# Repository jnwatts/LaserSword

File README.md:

# LaserSword
Advanced replacement logic board for a $7 "laser sword"

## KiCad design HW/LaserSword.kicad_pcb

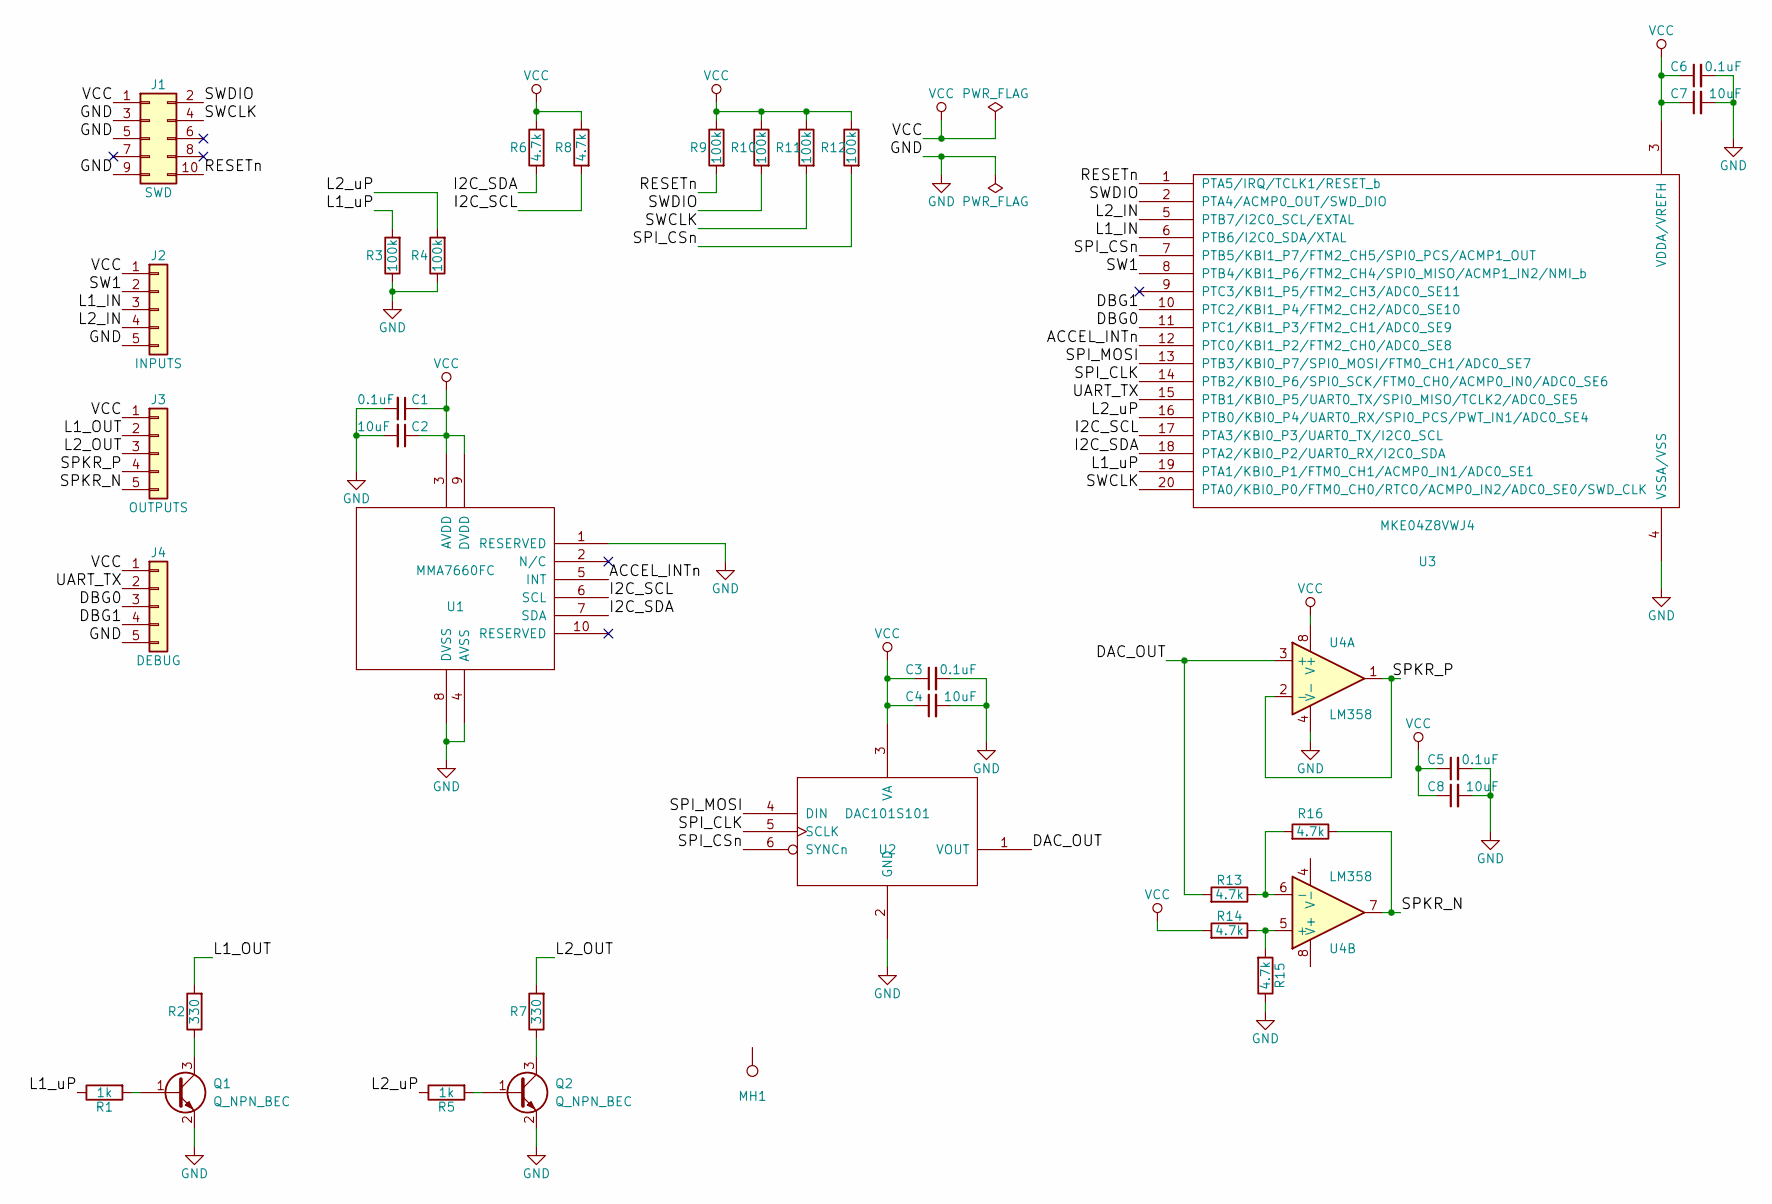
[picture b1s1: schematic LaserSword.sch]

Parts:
C1, C3, C5, C6: 0.1uF; C_0603_HandSoldering
C2, C4, C7, C8: 10uF; C_0603_HandSoldering
J1: SWD; Pin_Header_Straight_2x05_Pitch1.27mm; digikey# SAM9430-ND
J2: INPUTS; Pin_Header_Straight_1x05_Pitch1.00mm; MfrPart SMH100-LPSE-Sxx-ST-BK; digikey# S9215-ND
J3: OUTPUTS; Pin_Header_Straight_1x05_Pitch1.00mm; MfrPart SMH100-LPSE-Sxx-ST-BK; digikey# S9215-ND
J4: DEBUG; Pin_Header_Straight_1x05_Pitch1.00mm; MfrPart SMH100-LPSE-Sxx-ST-BK; digikey# S9215-ND
MH1: MH1; MountingHole_2.2mm_M2
Q1, Q2: Q_NPN_BEC; SOT-23; MfrPart MMBT3904TPMSCT; digikey# MMBT3904TPMSCT-ND
R1, R5: 1k; R_0603_HandSoldering
R2, R7: 330; R_0603_HandSoldering
R3, R4, R9, R10, R11, R12: 100k; R_0603_HandSoldering
R6, R8, R13, R14, R15, R16: 4.7k; R_0603_HandSoldering
U1: MMA7660FC; DFN-10_3x3mm_Pitch0.5mm; MfrPart MMA7660FCT; digikey# MMA7660FCT-ND
U2: DAC101S101; SOT-23-6_Handsoldering; MfrPart DAC101S101CIMK/NOPB; digikey# DAC101S101CIMK/NOPBCT-ND
U3: MKE04Z8VWJ4; SO-20_12.8x7.5mm_Pitch1.27mm; MfrPart MKE04Z8VWJ4; digikey# MKE04Z8VWJ4-ND
U4: LM358; SOIC-8_3.9x4.9mm_Pitch1.27mm; MfrPart LMV358DR2G; digikey# LMV358DR2GOSCT-ND

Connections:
/ACCEL_INTn: U1.5 (INT), U3.12 (PTC0/KBI1_P2/FTM2_CH0/ADC0_SE8)
/DAC_OUT: R13.2, U2.1 (VOUT), U4.3 (+)
/DBG0: J4.3, U3.11 (PTC1/KBI1_P3/FTM2_CH1/ADC0_SE9)
/DBG1: J4.4, U3.10 (PTC2/KBI1_P4/FTM2_CH2/ADC0_SE10)
/I2C_SCL: R8.2, U1.6 (SCL), U3.17 (PTA3/KBI0_P3/UART0_TX/I2C0_SCL)
/I2C_SDA: R6.2, U1.7 (SDA), U3.18 (PTA2/KBI0_P2/UART0_RX/I2C0_SDA)
/L1_IN: J2.3, U3.6 (PTB6/I2C0_SDA/XTAL)
/L1_OUT: J3.2, R2.2
/L1_uP: R1.1, R3.2, U3.19 (PTA1/KBI0_P1/FTM0_CH1/ACMP0_IN1/ADC0_SE1)
/L2_IN: J2.4, U3.5 (PTB7/I2C0_SCL/EXTAL)
/L2_OUT: J3.3, R7.2
/L2_uP: R4.2, R5.1, U3.16 (PTB0/KBI0_P4/UART0_RX/SPI0_PCS/PWT_IN1/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)
/RESETn: J1.10, R9.2, U3.1 (PTA5/IRQ/TCLK1/RESET_b)
/SPI_CLK: U2.5 (SCLK), U3.14 (PTB2/KBI0_P6/SPI0_SCK/FTM0_CH0/ACMP0_IN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)
/SPI_CSn: R12.2, U2.6 (SYNCn), U3.7 (PTB5/KBI1_P7/FTM2_CH5/SPI0_PCS/ACMP1_OUT)
/SPI_MOSI: U2.4 (DIN), U3.13 (PTB3/KBI0_P7/SPI0_MOSI/FTM0_CH1/ADC0_SE7)
/SPKR_N: J3.5, R16.1, U4.7
/SPKR_P: J3.4, U4.1, U4.2 (-)
/SW1: J2.2, U3.8 (PTB4/KBI1_P6/FTM2_CH4/SPI0_MISO/ACMP1_I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)
/SWCLK: J1.4, R11.2, U3.20 (PTA0/KBI0_P0/FTM0_CH0/RTCO/ACMP0_IN2/AD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)
/SWDIO: J1.2, R10.2, U3.2 (PTA4/ACMP0_OUT/SWD_DIO)
/UART_TX: J4.2, U3.15 (PTB1/KBI0_P5/UART0_TX/SPI0_MISO/TCLK2/A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)
GND: C1.2, C2.2, C3.2, C4.2, C5.2, C6.2, C7.2, C8.2, J1.3, J1.5, J1.9, J2.5, J4.5, Q1.2 (E), Q2.2 (E), R3.1, R4.1, R15.1, U1.1 (RESERVED), U1.4 (AVSS), U1.8 (DVSS), U2.2 (GND), U3.4 (VSSA/VSS), U4.4 (V-)
unnamed: Q1.1 (B), R1.2
unnamed: Q1.3 (C), R2.1
unnamed: Q2.1 (B), R5.2
unnamed: Q2.3 (C), R7.1
unnamed: R13.1, R16.2, U4.6 (-)
unnamed: R14.1, R15.2, U4.5 (+)
VCC: C1.1, C2.1, C3.1, C4.1, C5.1, C6.1, C7.1, C8.1, J1.1, J2.1, J3.1, J4.1, R6.1, R8.1, R9.1, R10.1, R11.1, R12.1, R14.2, U1.3 (AVDD), U1.9 (DVDD), U2.3 (VA), U3.3 (VDDA/VREFH), U4.8 (V+)

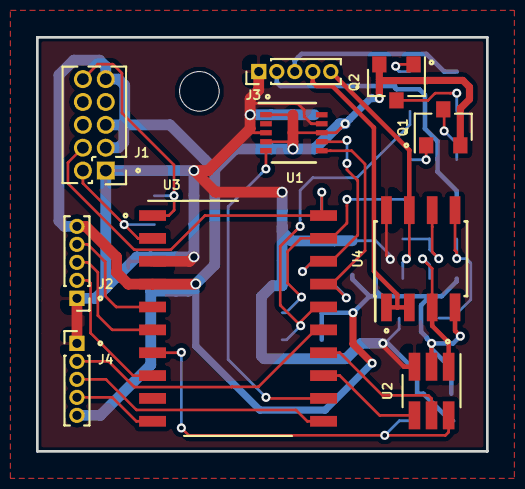
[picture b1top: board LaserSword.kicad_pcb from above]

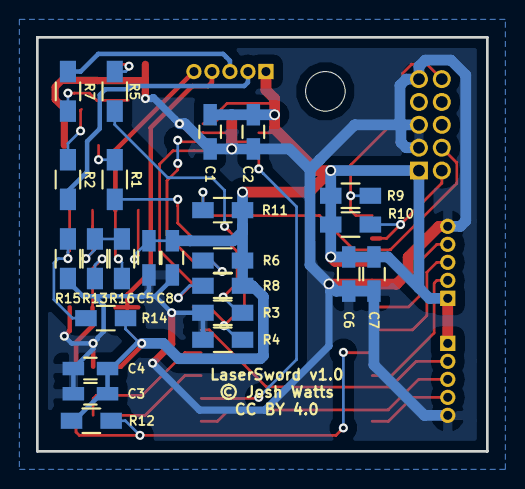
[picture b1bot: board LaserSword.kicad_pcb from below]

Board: 2 copper layers, 25.0 x 23.0 mm, 35 parts (24 on the bottom side), 30 nets.

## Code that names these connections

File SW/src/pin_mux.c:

/***********************************************************************************************************************
 * This file was generated by the MCUXpresso Config Tools. Any manual edits made to this file
 * will be overwritten if the respective MCUXpresso Config Tools is used to update this file.
 **********************************************************************************************************************/

/* clang-format off */
/*
 * TEXT BELOW IS USED AS SETTING FOR TOOLS *************************************
!!GlobalInfo
product: Pins v4.0
processor: MKE04Z8xxx4
package_id: MKE04Z8VWJ4
mcu_data: ksdk2_0
processor_version: 3.0.0
pin_labels:
- {pin_num: '5', pin_signal: PTB7/I2C0_SCL/EXTAL, label: L2_IN}
- {pin_num: '6', pin_signal: PTB6/I2C0_SDA/XTAL, label: L1_IN}
- {pin_num: '8', pin_signal: PTB4/KBI1_P6/FTM2_CH4/SPI0_MISO/ACMP1_IN2/NMI_b, label: SW1}
- {pin_num: '9', pin_signal: PTC3/KBI1_P5/FTM2_CH3/ADC0_SE11, label: NC0}
- {pin_num: '10', pin_signal: PTC2/KBI1_P4/FTM2_CH2/ADC0_SE10, label: DBG1}
- {pin_num: '11', pin_signal: PTC1/KBI1_P3/FTM2_CH1/ADC0_SE9, label: DBG0}
- {pin_num: '12', pin_signal: PTC0/KBI1_P2/FTM2_CH0/ADC0_SE8, label: ACCEL_INTn}
- {pin_num: '16', pin_signal: PTB0/KBI0_P4/UART0_RX/SPI0_PCS0/PWT_IN1/ADC0_SE4, label: L2_uP}
- {pin_num: '19', pin_signal: PTA1/KBI0_P1/FTM0_CH1/ACMP0_IN1/ADC0_SE1, label: L1_uP}
 * BE CAREFUL MODIFYING THIS COMMENT - IT IS YAML SETTINGS FOR TOOLS ***********
 */
/* clang-format on */

#include "fsl_common.h"
#include "fsl_port.h"
#include "pin_mux.h"

/* FUNCTION ************************************************************************************************************
 *
 * Function Name : BOARD_InitBootPins
 * Description   : Calls initialization functions.
 *
 * END ****************************************************************************************************************/
void BOARD_InitBootPins(void)
{
    BOARD_InitPins();
}

/* clang-format off */
/*
 * TEXT BELOW IS USED AS SETTING FOR TOOLS *************************************
BOARD_InitPins:
- options: {callFromInitBoot: 'true', coreID: core0, enableClock: 'true'}
- pin_list:
  - {pin_num: '1', peripheral: SystemControl, signal: RESET, pin_signal: PTA5/IRQ/TCLK1/RESET_b}
  - {pin_num: '5', peripheral: GPIOA, signal: 'GPIO, 15', pin_signal: PTB7/I2C0_SCL/EXTAL}
  - {pin_num: '6', peripheral: GPIOA, signal: 'GPIO, 14', pin_signal: PTB6/I2C0_SDA/XTAL}
  - {pin_num: '14', peripheral: SPI0, signal: SCK, pin_signal: PTB2/KBI0_P6/SPI0_SCK/FTM0_CH0/ACMP0_IN0/ADC0_SE6}
  - {pin_num: '13', peripheral: SPI0, signal: MOSI, pin_signal: PTB3/KBI0_P7/SPI0_MOSI/FTM0_CH1/ADC0_SE7}
  - {pin_num: '7', peripheral: SPI0, signal: PCS, pin_signal: PTB5/KBI1_P7/FTM2_CH5/SPI0_PCS0/ACMP1_OUT}
  - {pin_num: '15', peripheral: UART0, signal: TX, pin_signal: PTB1/KBI0_P5/UART0_TX/SPI0_MISO/TCLK2/ADC0_SE5}
  - {pin_num: '18', peripheral: I2C0, signal: SDA, pin_signal: PTA2/KBI0_P2/UART0_RX/I2C0_SDA}
  - {pin_num: '17', peripheral: I2C0, signal: SCL, pin_signal: PTA3/KBI0_P3/UART0_TX/I2C0_SCL}
  - {pin_num: '19', peripheral: GPIOA, signal: 'GPIO, 1', pin_signal: PTA1/KBI0_P1/FTM0_CH1/ACMP0_IN1/ADC0_SE1}
  - {pin_num: '20', peripheral: CoreDebug, signal: SWD_CLK, pin_signal: PTA0/KBI0_P0/FTM0_CH0/RTCO/ACMP0_IN2/ADC0_SE0/SWD_CLK}
  - {pin_num: '2', peripheral: CoreDebug, signal: SWD_DIO, pin_signal: PTA4/ACMP0_OUT/SWD_DIO}
  - {pin_num: '8', peripheral: GPIOA, signal: 'GPIO, 12', pin_signal: PTB4/KBI1_P6/FTM2_CH4/SPI0_MISO/ACMP1_IN2/NMI_b}
  - {pin_num: '10', peripheral: GPIOA, signal: 'GPIO, 18', pin_signal: PTC2/KBI1_P4/FTM2_CH2/ADC0_SE10}
  - {pin_num: '11', peripheral: GPIOA, signal: 'GPIO, 17', pin_signal: PTC1/KBI1_P3/FTM2_CH1/ADC0_SE9}
  - {pin_num: '12', peripheral: GPIOA, signal: 'GPIO, 16', pin_signal: PTC0/KBI1_P2/FTM2_CH0/ADC0_SE8}
  - {pin_num: '16', peripheral: GPIOA, signal: 'GPIO, 8', pin_signal: PTB0/KBI0_P4/UART0_RX/SPI0_PCS0/PWT_IN1/ADC0_SE4}
  - {pin_num: '9', peripheral: GPIOA, signal: 'GPIO, 19', pin_signal: PTC3/KBI1_P5/FTM2_CH3/ADC0_SE11}
  - {pin_num: '3', peripheral: SUPPLY, signal: 'VDD, 0', pin_signal: VDD}
  - {pin_num: '3', peripheral: ADC, signal: VDDA, pin_signal: VDDA/VREFH}
  - {pin_num: '4', peripheral: ADC, signal: VREFL, pin_signal: VREFL}
  - {pin_num: '4', peripheral: SUPPLY, signal: 'VSS, 0', pin_signal: VSSA/VSS}
  - {pin_num: '3', peripheral: ADC, signal: VREFH, pin_signal: VDDA/VREFH}
  - {pin_num: '4', peripheral: ADC, signal: VSSA, pin_signal: VSSA/VSS}
 * BE CAREFUL MODIFYING THIS COMMENT - IT IS YAML SETTINGS FOR TOOLS ***********
 */
/* clang-format on */

/* FUNCTION ************************************************************************************************************
 *
 * Function Name : BOARD_InitPins
 * Description   : Configures pin routing and optionally pin electrical features.
 *
 * END ****************************************************************************************************************/
void BOARD_InitPins(void)
{
    /* pin 18,17 is configured as I2C0_SDA, I2C0_SCL */
    PORT_SetPinSelect(kPORT_I2C0, kPORT_I2C0_SCLPTA3_SDAPTA2);
    /* pin 14,7,13 is configured as SPI0_SCK, SPI0_PCS0, SPI0_MOSI */
    PORT_SetPinSelect(kPORT_SPI0, kPORT_SPI0_SCKPTB2_MOSIPTB3_MISOPTB4_PCSPTB5);
    /* pin 15 is configured as UART0_TX */
    PORT_SetPinSelect(kPORT_UART0, kPORT_UART0_RXPTB0_TXPTB1);
}
/***********************************************************************************************************************
 * EOF
 **********************************************************************************************************************/

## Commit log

2018-01-11 Initial commit with 1st pass at schematic
2018-01-14 First pass at layout
2018-01-15 Refactor to use NPN
2018-01-16 Add opamp circuit
2018-01-17 Rebuilt with dual opamp, diff. speaker drive
2018-01-25 Add PDF of schematic
2018-01-25 Initial commit from project template
    Some minor changes to resolve build issues, and set -DCPU_MKE04Z8VWJ4
2018-01-25 Add pin_mux
2018-01-25 Move main to main.c where it belongs
2018-01-25 Customize board config
2018-01-25 Minimal main() example with proper initialization
2018-01-25 Uppdate clock_config
2018-02-02 Rename build scripts to better mirror their purpose
2018-02-03 clock: Default to FullSpeed
    LowPower is tripping some kind of hard fault: LP is an optimization for later
2018-02-03 board: Define GPIO pins from schematic
2018-02-04 Add fsl_ftm driver
2018-02-04 Implement led control
2018-02-04 main: Implement 100Hz/10ms logic loop
2018-02-04 Oops, PinInit() uses pin-number, not mask
2018-02-04 Add sd_fat module
2018-02-04 Add TODO
2018-02-04 TODO: Note slow GPIO driver
2018-02-04 clock_config: Update metadata
2018-02-04 main: Integrate led control
2018-02-04 Add sublime to gitignore
2018-02-04 Move FTM logic to Timer module
2018-02-04 Implement button logic
2018-02-04 main: Integrate button logic
2018-02-04 Limit stack and heap size
2018-02-04 TODO: Note LowPower() issues
2018-02-04 Buttons: Implement delayed button press logic
2018-02-04 Leds: Mark first & last colors
2018-02-04 main: Allow user to select next color by holding SW1 for >500ms
2018-02-04 Update TODO

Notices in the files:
HW/LaserSword.kicad_pcb:
© Josh Watts
CC BY 4.0
